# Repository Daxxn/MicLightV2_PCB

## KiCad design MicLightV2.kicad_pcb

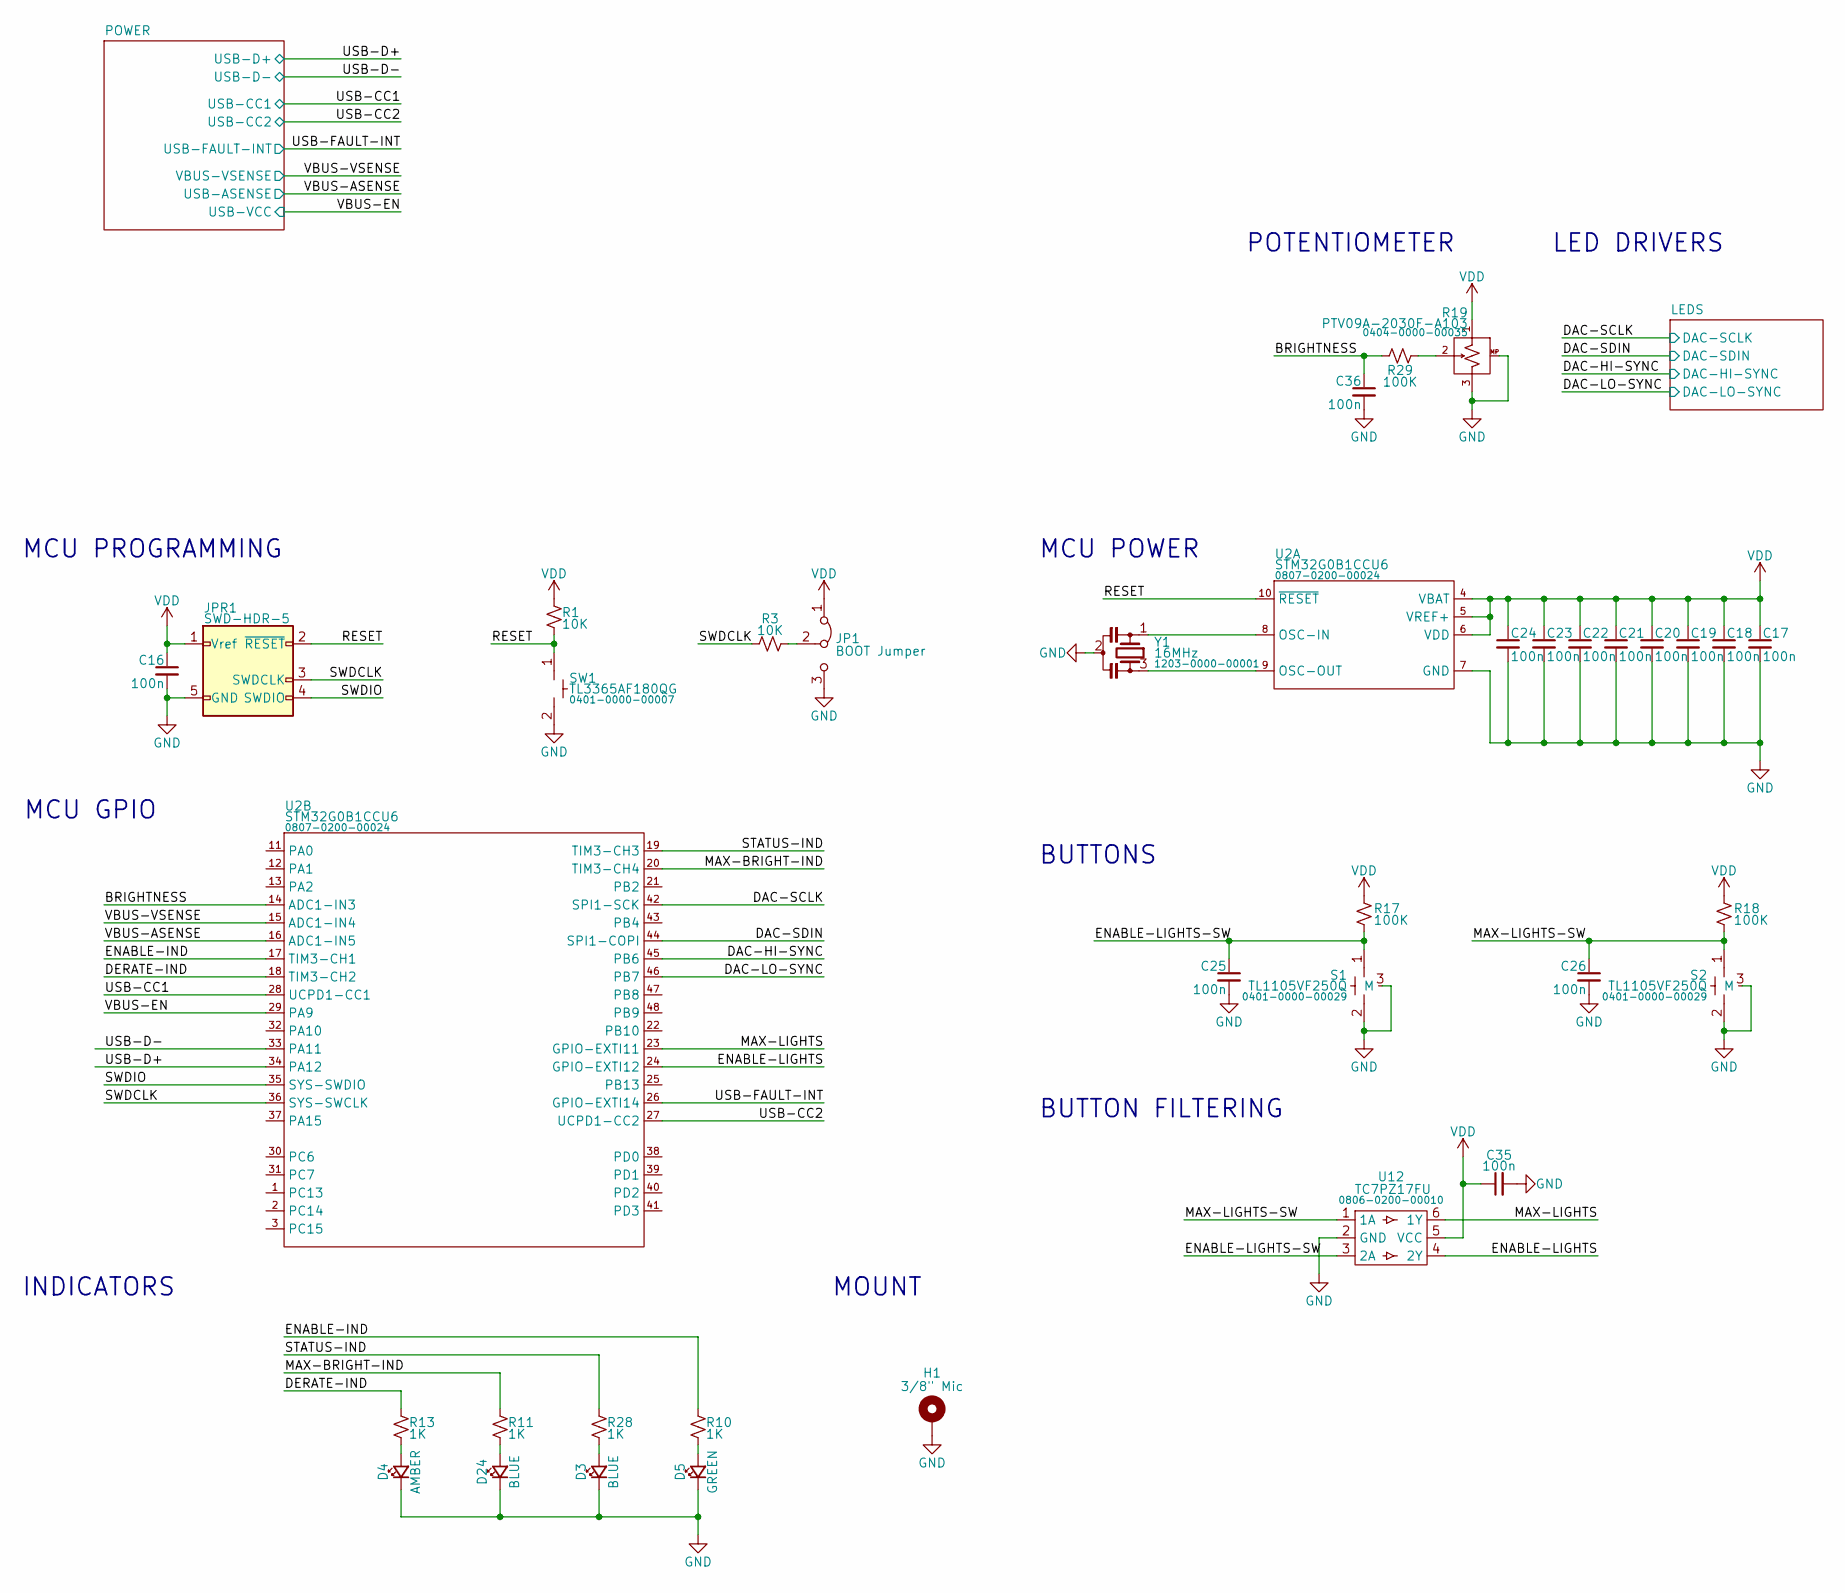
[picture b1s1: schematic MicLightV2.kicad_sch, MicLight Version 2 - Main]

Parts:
C16, C17, C18, C19, C20, C21, C22, C23, C24, C25, C26, C35, C36: 100n; CAP_0402; PartNumber 0201-0100-00001
D3, D24: LTST-S321TBKT; PartNumber 0902-0000-00004
D4: IN-S63AS5UW; LTST-S321TBKT; PartNumber 0902-0000-00002
D5: SM1204SGC; LTST-S321TBKT; PartNumber 0902-0000-00005
H1: 3/8" Mic; MountingHole_0.375in_Mic_Stand
JP1: BOOT Jumper; SolderJumper-3_P1.3mm_Open_RoundedPad1.0x1.5mm
JPR1: SWD-HDR-5; PinHeader_1x05_P2.54mm_Vertical
R1, R3: 10K; RES_0402; PartNumber 0204-0000-00016
R10, R11, R13, R28: 1K; RES_0402; PartNumber 0204-0000-00032
R17, R18, R29: 100K; RES_0402; PartNumber 0204-0000-00013
R19: PTV09A-2030F-A103; PartNumber 0404-0000-00035
S1, S2: TL1105VF250Q; TL1105VF; PartNumber 0401-0000-00029
SW1: TL3365AF180QG; PartNumber 0401-0000-00007
U2: STM32G0B1CCU6; QFN-48-1EP_7x7mm_P0.5mm_EP5.6x5.6mm; PartNumber 0807-0200-00024
U12: TC7PZ17FU; SOT-363_SC-70-6; PartNumber 0806-0200-00010
Y1: 16MHz; Resonator_SMD_3Pin_3.0x1.1mm; PartNumber 1203-0000-00001

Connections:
/BRIGHTNESS: C36.1, R29.1, U2.14 (PA3)
/DAC-HI-SYNC: U2.45 (PB6); also elsewhere on the board
/DAC-LO-SYNC: U2.46 (PB7); also elsewhere on the board
/DAC-SCLK: U2.42 (SPI1-SCK); also elsewhere on the board
/DAC-SDIN: U2.44 (SPI1-COPI); also elsewhere on the board
/DERATE-IND: R13.1, U2.18 (TIM3-CH2)
/ENABLE-IND: R10.1, U2.17 (TIM3-CH1)
/ENABLE-LIGHTS: U2.24 (GPIO-EXTI12), U12.4 (2Y)
/ENABLE-LIGHTS-SW: C25.1, R17.2, S1.1, U12.3 (2A)
/MAX-BRIGHT-IND: R11.1, U2.20 (TIM3-CH4)
/MAX-LIGHTS: U2.23 (GPIO-EXTI11), U12.6 (1Y)
/MAX-LIGHTS-SW: C26.1, R18.2, S2.1, U12.1 (1A)
/RESET: JPR1.2 (~RESET), R1.2, SW1.1, U2.10 (~RESET)
/STATUS-IND: R28.1, U2.19 (TIM3-CH3)
/SWDCLK: JPR1.3 (SWDCLK), R3.1, U2.36 (SYS-SWCLK)
/SWDIO: JPR1.4 (SWDIO), U2.35 (SYS-SWDIO)
/USB-CC1: U2.28 (UCPD1-CC1); also elsewhere on the board
/USB-CC2: U2.27 (UCPD1-CC2); also elsewhere on the board
/USB-D+: U2.34 (PA12); also elsewhere on the board
/USB-D-: U2.33 (PA11); also elsewhere on the board
/USB-FAULT-INT: U2.26 (GPIO-EXTI14); also elsewhere on the board
/VBUS-ASENSE: U2.16 (PA5); also elsewhere on the board
/VBUS-VSENSE: U2.15 (PA4); also elsewhere on the board
GND: C16.2, C17.2, C18.2, C19.2, C20.2, C21.2, C22.2, C23.2, C24.2, C25.2, C26.2, C35.2, C36.2, D3.1 (K), D4.1 (K), D5.1 (K), D24.1 (K), H1.1, JP1.3 (B), JPR1.5 (GND), R19.3 (B), R19.MP (Mount), S1.2, S1.3 (M), S2.2, S2.3 (M), SW1.2, U2.7 (GND), U2.49 (GND), U12.2 (GND), Y1.2; also elsewhere on the board
unnamed: D3.2 (A), R28.2
unnamed: D4.2 (A), R13.2
unnamed: D5.2 (A), R10.2
unnamed: D24.2 (A), R11.2
unnamed: JP1.2 (C), R3.2
unnamed: R19.2 (W), R29.2
unnamed: U2.8 (OSC-IN), Y1.1
unnamed: U2.9 (OSC-OUT), Y1.3
VDD: C16.1, C17.1, C18.1, C19.1, C20.1, C21.1, C22.1, C23.1, C24.1, C35.1, JP1.1 (A), JPR1.1 (Vref), R1.1, R17.1, R18.1, R19.1 (A), U2.4 (VBAT), U2.5 (VREF+), U2.6 (VDD), U12.5 (VCC); also elsewhere on the board

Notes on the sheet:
MCU GPIO
BUTTON FILTERING
INDICATORS
LED DRIVERS
POTENTIOMETER
MCU POWER
MCU PROGRAMMING
MOUNT
BUTTONS

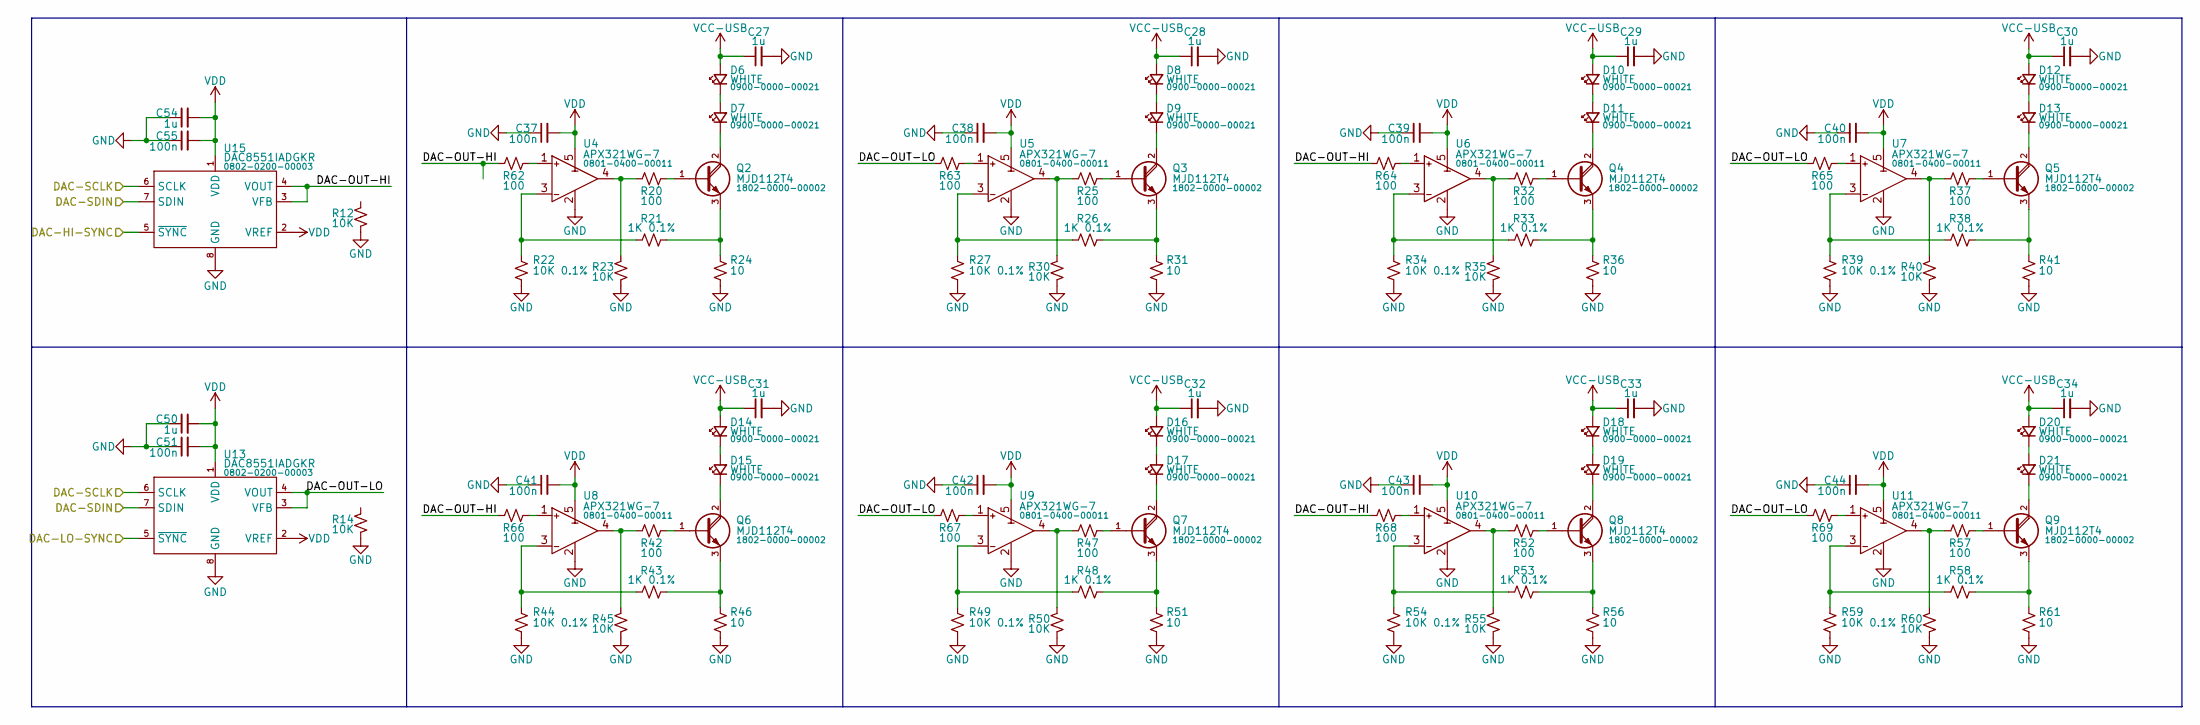
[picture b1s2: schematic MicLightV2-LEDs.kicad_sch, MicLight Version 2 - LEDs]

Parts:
C27, C28, C29, C30, C31, C32, C33, C34: 1u; CAP_0603; PartNumber 0201-0100-00051
C37, C38, C39, C40, C41, C42, C43, C44, C51, C55: 100n; CAP_0402; PartNumber 0201-0100-00001
C50, C54: 1u; CAP_0402; PartNumber 0201-0100-00050
D6, D7, D8, D9, D10, D11, D12, D13, D14, D15, D16, D17, D18, D19, D20, D21: JK3030AWT-P-H40EA0000-N0000001; JK3030AWT; PartNumber 0900-0000-00021
Q2, Q3, Q4, Q5, Q6, Q7, Q8, Q9: MJD112T4; TO-252-2; PartNumber 1802-0000-00002
R12, R14, R23, R30, R35, R40, R45, R50, R55, R60: 10K; RES_0402; PartNumber 0204-0000-00016
R20, R25, R32, R37, R42, R47, R52, R57: 100; RES_0402
R21, R26, R33, R38, R43, R48, R53, R58: 1K 0.1%; RES_0402; PartNumber 0204-0100-00012
R22, R27, R34, R39, R44, R49, R54, R59: 10K 0.1%; RES_0402; PartNumber 0204-0100-00019
R24, R31, R36, R41, R46, R51, R56, R61: 10; RES_1218; PartNumber 0204-0200-00031
R62, R63, R64, R65, R66, R67, R68, R69: 100; RES_0402; PartNumber 0204-0000-00011
U4, U5, U6, U7, U8, U9, U10, U11: APX321WG-7; SOT-23-5; PartNumber 0801-0400-00011
U13, U15: DAC8551IADGKR; VSSOP-8_3.0x3.0mm_P0.65mm; PartNumber 0802-0200-00003

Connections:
/DAC-HI-SYNC: U15.5 (~SYNC); also elsewhere on the board
/DAC-LO-SYNC: U13.5 (~SYNC); also elsewhere on the board
/DAC-SCLK: U13.6 (SCLK), U15.6 (SCLK); also elsewhere on the board
/DAC-SDIN: U13.7 (SDIN), U15.7 (SDIN); also elsewhere on the board
/LEDS/DAC-OUT-HI: R62.1, R64.1, R66.1, R68.1, U15.3 (VFB), U15.4 (VOUT)
/LEDS/DAC-OUT-LO: R63.1, R65.1, R67.1, R69.1, U13.3 (VFB), U13.4 (VOUT)
GND: C27.2, C28.2, C29.2, C30.2, C31.2, C32.2, C33.2, C34.2, C37.1, C38.1, C39.1, C40.1, C41.1, C42.1, C43.1, C44.1, C50.1, C51.1, C54.1, C55.1, R12.2, R14.2, R22.2, R23.2, R24.2, R27.2, R30.2, R31.2, R34.2, R35.2, R36.2, R39.2, R40.2, R41.2, R44.2, R45.2, R46.2, R49.2, R50.2, R51.2, R54.2, R55.2, R56.2, R59.2, R60.2, R61.2, U4.2 (V-), U5.2 (V-), U6.2 (V-), U7.2 (V-), U8.2 (V-), U9.2 (V-), U10.2 (V-), U11.2 (V-), U13.8 (GND), U15.8 (GND); also elsewhere on the board
unnamed: D6.1 (K), D7.2 (A)
unnamed: D7.1 (K), Q2.2 (C)
unnamed: D8.1 (K), D9.2 (A)
unnamed: D9.1 (K), Q3.2 (C)
unnamed: D10.1 (K), D11.2 (A)
unnamed: D11.1 (K), Q4.2 (C)
unnamed: D12.1 (K), D13.2 (A)
unnamed: D13.1 (K), Q5.2 (C)
unnamed: D14.1 (K), D15.2 (A)
unnamed: D15.1 (K), Q6.2 (C)
unnamed: D16.1 (K), D17.2 (A)
unnamed: D17.1 (K), Q7.2 (C)
unnamed: D18.1 (K), D19.2 (A)
unnamed: D19.1 (K), Q8.2 (C)
unnamed: D20.1 (K), D21.2 (A)
unnamed: D21.1 (K), Q9.2 (C)
unnamed: Q2.1 (B), R20.2
unnamed: Q2.3 (E), R21.2, R24.1
unnamed: Q3.1 (B), R25.2
unnamed: Q3.3 (E), R26.2, R31.1
unnamed: Q4.1 (B), R32.2
unnamed: Q4.3 (E), R33.2, R36.1
unnamed: Q5.1 (B), R37.2
unnamed: Q5.3 (E), R38.2, R41.1
unnamed: Q6.1 (B), R42.2
unnamed: Q6.3 (E), R43.2, R46.1
unnamed: Q7.1 (B), R47.2
unnamed: Q7.3 (E), R48.2, R51.1
unnamed: Q8.1 (B), R52.2
unnamed: Q8.3 (E), R53.2, R56.1
unnamed: Q9.1 (B), R57.2
unnamed: Q9.3 (E), R58.2, R61.1
unnamed: R62.2, U4.1 (IN+)
unnamed: R21.1, R22.1, U4.3 (IN-)
unnamed: R20.1, R23.1, U4.4 (OUT)
unnamed: R63.2, U5.1 (IN+)
unnamed: R26.1, R27.1, U5.3 (IN-)
unnamed: R25.1, R30.1, U5.4 (OUT)
unnamed: R64.2, U6.1 (IN+)
unnamed: R33.1, R34.1, U6.3 (IN-)
unnamed: R32.1, R35.1, U6.4 (OUT)
unnamed: R65.2, U7.1 (IN+)
unnamed: R38.1, R39.1, U7.3 (IN-)
unnamed: R37.1, R40.1, U7.4 (OUT)
unnamed: R66.2, U8.1 (IN+)
unnamed: R43.1, R44.1, U8.3 (IN-)
unnamed: R42.1, R45.1, U8.4 (OUT)
unnamed: R67.2, U9.1 (IN+)
unnamed: R48.1, R49.1, U9.3 (IN-)
unnamed: R47.1, R50.1, U9.4 (OUT)
unnamed: R68.2, U10.1 (IN+)
unnamed: R53.1, R54.1, U10.3 (IN-)
unnamed: R52.1, R55.1, U10.4 (OUT)
unnamed: R69.2, U11.1 (IN+)
unnamed: R58.1, R59.1, U11.3 (IN-)
unnamed: R57.1, R60.1, U11.4 (OUT)
VCC-USB: C27.1, C28.1, C29.1, C30.1, C31.1, C32.1, C33.1, C34.1, D6.2 (A), D8.2 (A), D10.2 (A), D12.2 (A), D14.2 (A), D16.2 (A), D18.2 (A), D20.2 (A); also elsewhere on the board
VDD: C37.2, C38.2, C39.2, C40.2, C41.2, C42.2, C43.2, C44.2, C50.2, C51.2, C54.2, C55.2, U4.5 (V+), U5.5 (V+), U6.5 (V+), U7.5 (V+), U8.5 (V+), U9.5 (V+), U10.5 (V+), U11.5 (V+), U13.1 (VDD), U13.2 (VREF), U15.1 (VDD), U15.2 (VREF); also elsewhere on the board

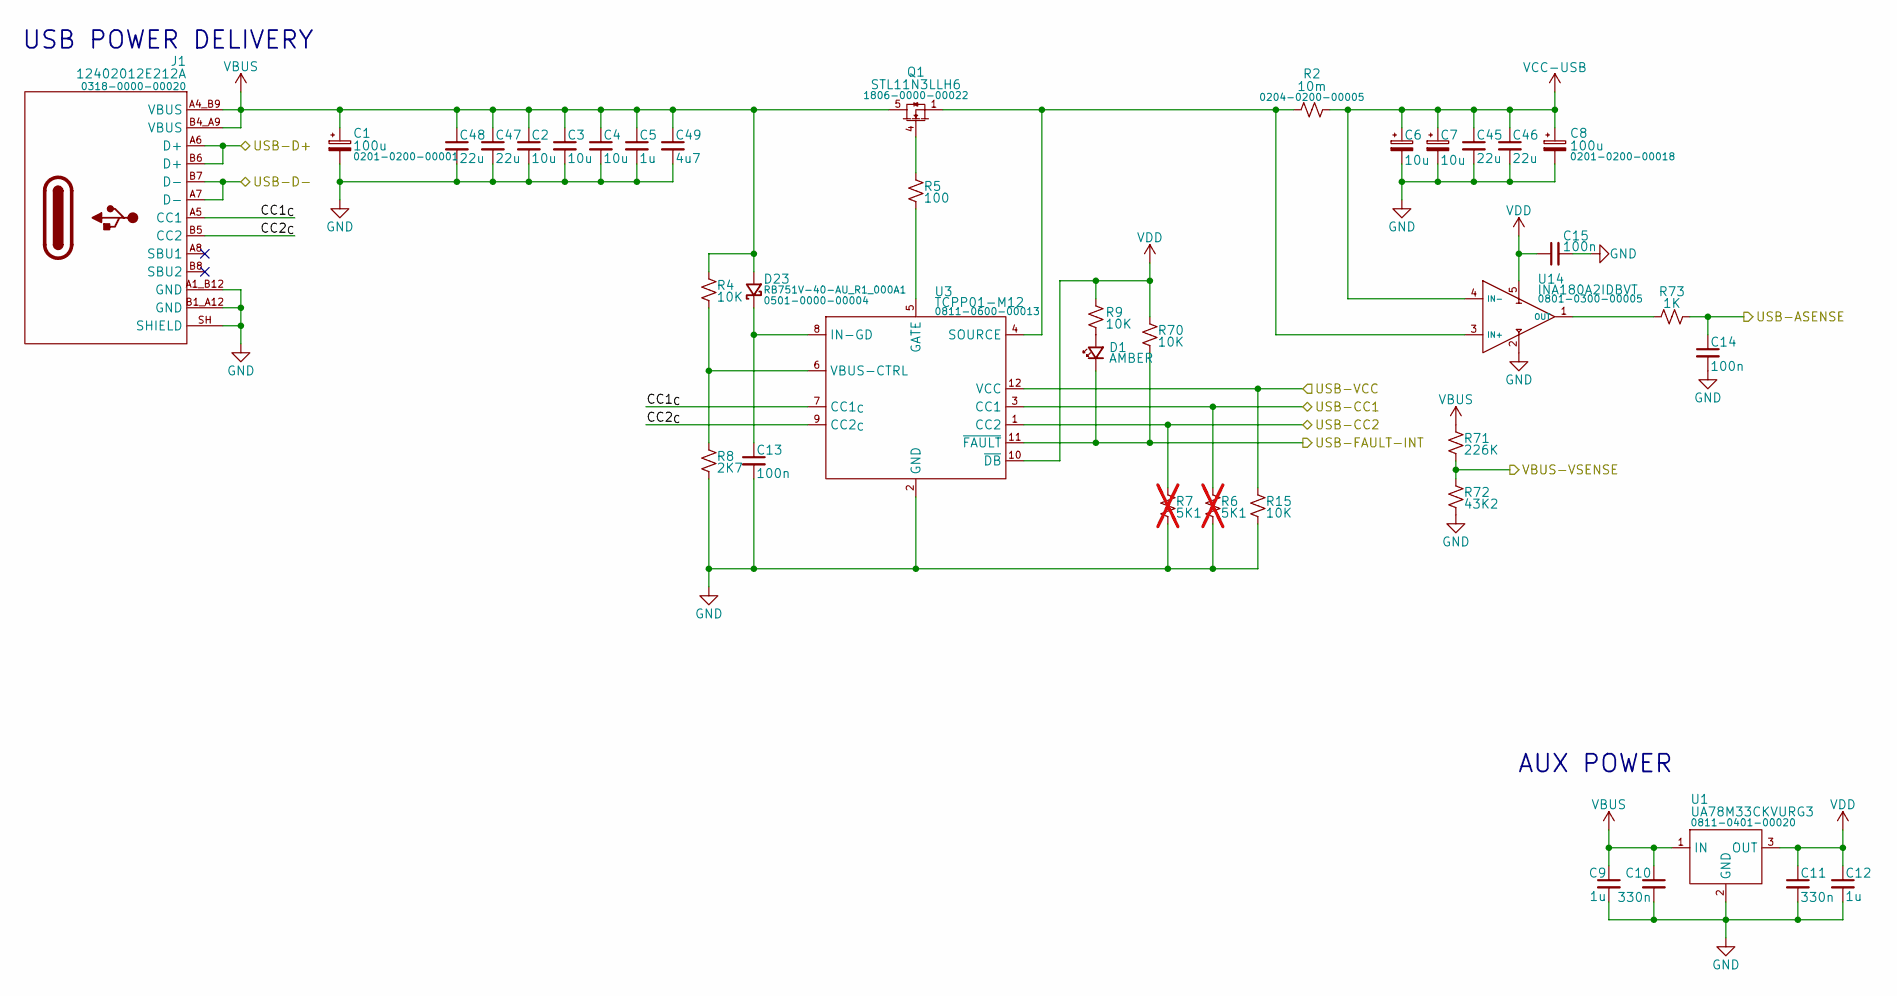
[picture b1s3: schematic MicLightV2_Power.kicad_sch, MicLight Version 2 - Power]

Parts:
C1: 100u; CAP_EL_8x10; PartNumber 0201-0200-00001
C2, C3, C4: 10u; CAP_1210; PartNumber 0201-0100-00040
C5, C9, C12: 1u; CAP_0603; PartNumber 0201-0100-00051
C6, C7: 10u; C-TANT-1210_EIA-3528; PartNumber 0201-0300-00008
C8: 100u; CAP_EL_6.3x7.7; PartNumber 0201-0200-00018
C10, C11: 330n; CAP_0402
C13, C15: 100n; CAP_0402; PartNumber 0201-0100-00001
C14: 100n; CAP_0402
C45, C46, C47, C48: 22u; CAP_1206; PartNumber 0201-0100-00067
C49: 4u7; CAP_0805; PartNumber 0201-0100-00074
D1: IN-S63AS5UW; LTST-S321TBKT; PartNumber 0902-0000-00002
D23: RB751V-40-AU_R1_000A1; D_SOD-323; PartNumber 0501-0000-00004
J1: 12402012E212A; PartNumber 0318-0000-00020
Q1: STL11N3LLH6; POWERFLAT_3.3MM; PartNumber 1806-0000-00022
R2: 10m; RES_1206; PartNumber 0204-0200-00005
R4, R9, R15, R70: 10K; RES_0402; PartNumber 0204-0000-00016
R5: 100; RES_0402; PartNumber 0204-0000-00011
R6, R7: 5K1; RES_0402; PartNumber 0204-0000-00115; not fitted
R8: 2K7; RES_0402; PartNumber 0204-0000-00121
R71: 226K; RES_0402; PartNumber 0204-0000-00048
R72: 43K2; RES_0402; PartNumber 0204-0000-00110
R73: 1K; RES_0402
U1: UA78M33CKVURG3; TO-252-2; PartNumber 0811-0401-00020
U3: TCPP01-M12; QFN-12-1EP_3x3mm_P0.5mm_EP1.45x1.45mm; PartNumber 0811-0600-00013
U14: INA180A2IDBVT; SOT-23-5; PartNumber 0801-0300-00005

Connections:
/POWER/CC1_{C}: J1.A5 (CC1), U3.7 (CC1_{C})
/POWER/CC2_{C}: J1.B5 (CC2), U3.9 (CC2_{C})
/USB-CC1: R6.1, U3.3 (CC1); also elsewhere on the board
/USB-CC2: R7.1, U3.1 (CC2); also elsewhere on the board
/USB-D+: J1.A6 (D+), J1.B6 (D+); also elsewhere on the board
/USB-D-: J1.A7 (D-), J1.B7 (D-); also elsewhere on the board
/USB-FAULT-INT: D1.1 (K), R70.2, U3.11 (~FAULT); also elsewhere on the board
/VBUS-ASENSE: C14.1, R73.2; also elsewhere on the board
/VBUS-VSENSE: R71.2, R72.1; also elsewhere on the board
GND: C1.2 (-), C2.2, C3.2, C4.2, C5.2, C6.2, C7.2, C8.2 (-), C9.2, C10.2, C11.2, C12.2, C13.2, C14.2, C15.2, C45.2, C46.2, C47.2, C48.2, C49.2, J1.A1_B12 (GND), J1.B1_A12 (GND), J1.SH (SHIELD), R6.2, R7.2, R8.2, R15.2, R72.2, U1.2 (GND), U3.2 (GND), U3.13 (GND), U14.2 (GND); also elsewhere on the board
unnamed: D1.2 (A), R9.2
unnamed: C13.1, D23.1 (K), U3.8 (IN-GD)
unnamed: Q1.4 (G), R5.1
unnamed: R5.2, U3.5 (GATE)
unnamed: R4.2, R8.1, U3.6 (VBUS-CTRL)
unnamed: R73.1, U14.1 (OUT)
S: Q1.1 (S), Q1.2 (S), Q1.3 (S), R2.1, U3.4 (SOURCE), U14.3 (IN+)
VBUS: C1.1 (+), C2.1, C3.1, C4.1, C5.1, C9.1, C10.1, C47.1, C48.1, C49.1, D23.2 (A), J1.A4_B9 (VBUS), J1.B4_A9 (VBUS), Q1.5 (D), R4.1, R71.1, U1.1 (IN)
VCC-USB: C6.1, C7.1, C8.1 (+), C45.1, C46.1, R2.2, U14.4 (IN-); also elsewhere on the board
VDD: C11.1, C12.1, C15.1, R9.1, R15.1, R70.1, U1.3 (OUT), U3.10 (~DB), U3.12 (VCC), U14.5 (VS); also elsewhere on the board

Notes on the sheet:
USB POWER DELIVERY
AUX POWER

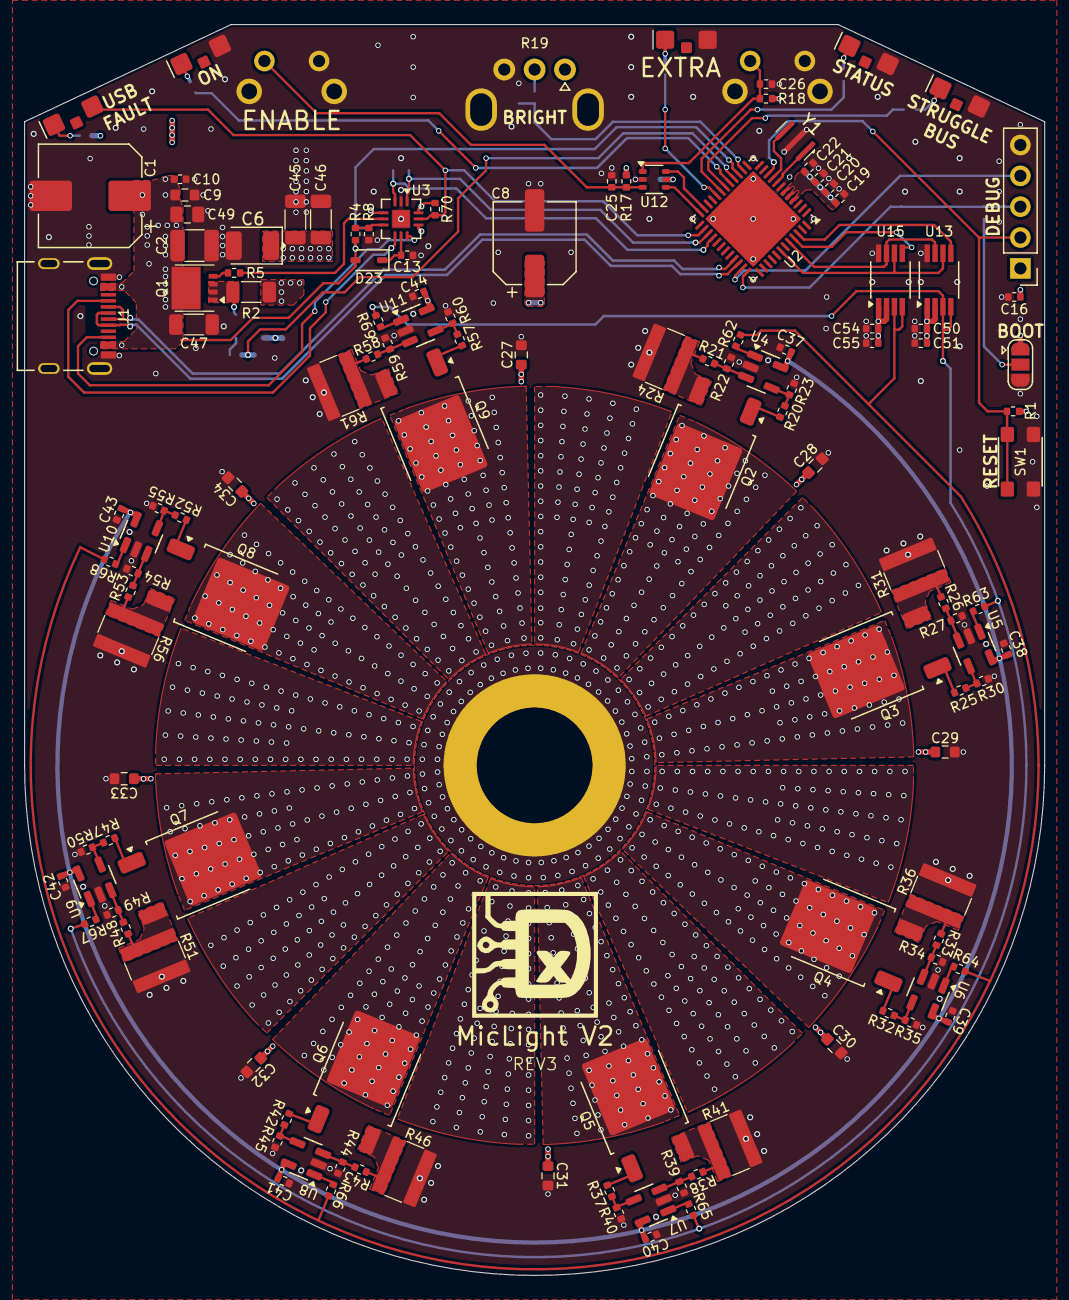
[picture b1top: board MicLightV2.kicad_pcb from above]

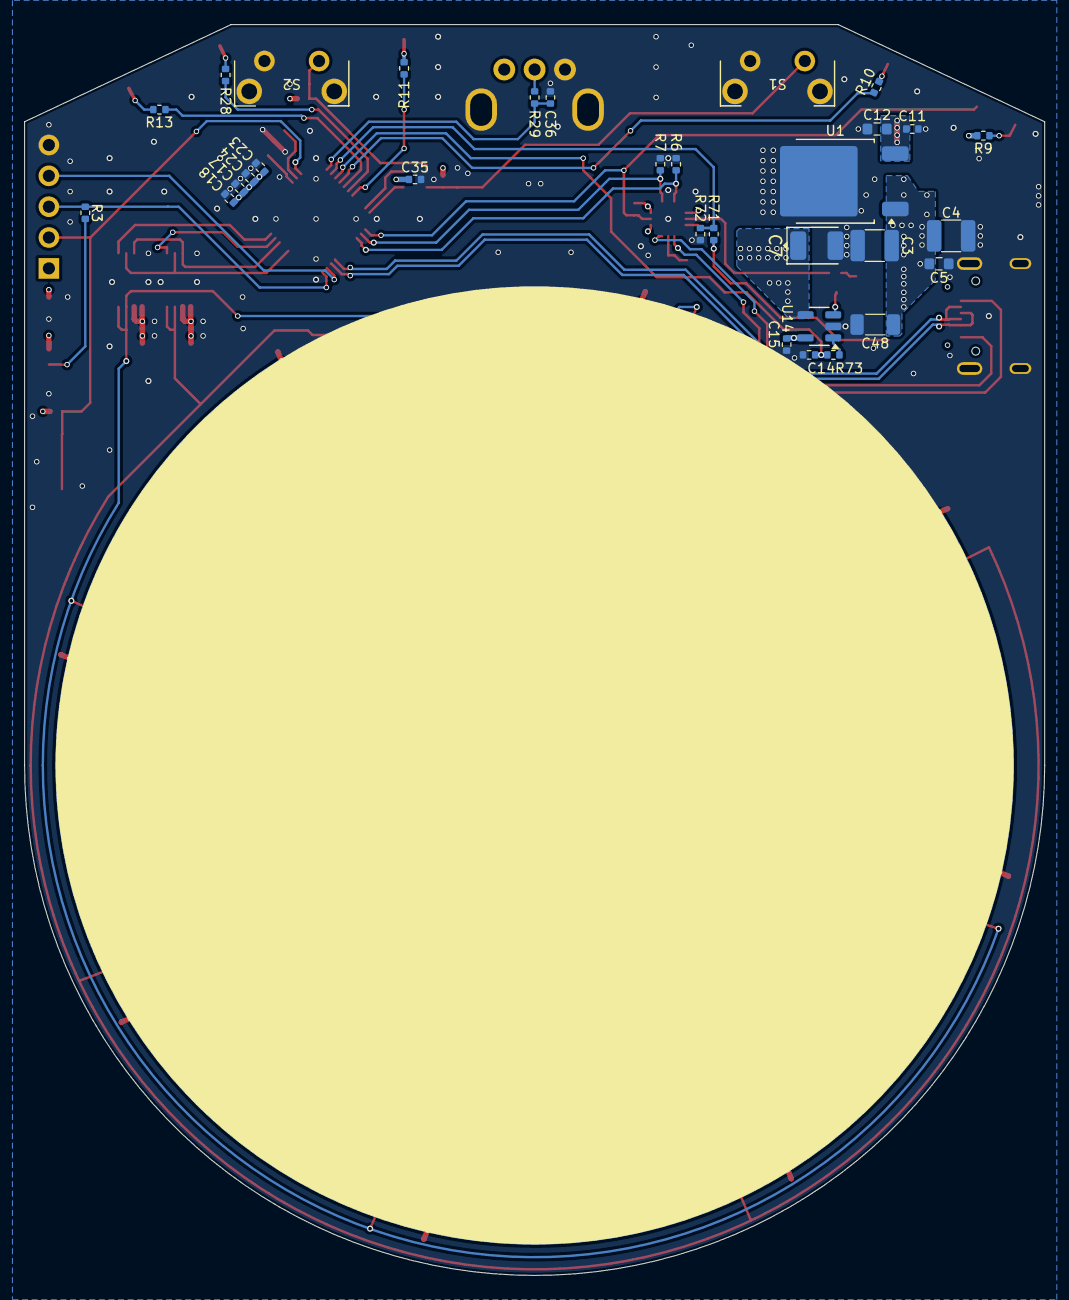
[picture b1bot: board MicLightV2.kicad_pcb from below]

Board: 4 copper layers, 84.0 x 103.0 mm, 176 parts (47 on the bottom side), 102 nets.

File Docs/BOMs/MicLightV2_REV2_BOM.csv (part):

"Reference","Value","PartNumber","Datasheet","Description","Color"
"C1","100u","0201-0200-00001","${DATASHEETS}/UWT.pdf","CAP ALUM 100uF 50V 140mA@120Hz ±20% SMD,D8xL10mm Aluminum Electrolytic Capacitors - SMD ROHS",""
"C2","10u","0201-0100-00040","${DATASHEETS}/CL32A106KAULNNE.pdf","CAP CER 10UF 25V X5R 1210",""
"C3","10u","0201-0100-00040","${DATASHEETS}/CL32A106KAULNNE.pdf","CAP CER 10UF 25V X5R 1210",""
"C4","10u","0201-0100-00040","${DATASHEETS}/CL32A106KAULNNE.pdf","CAP CER 10UF 25V X5R 1210",""
"C5","1u","0201-0100-00051","${DATASHEETS}/CL10A105KA8NNNC.pdf","CAP CER 1UF 25V X5R 0603",""
"C6","10u","0201-0300-00008","${DATASHEETS}/TCJ.pdf","10 µF Molded Tantalum Polymer Capacitor 35 V 1210 (3528 Metric) 200mOhm @ 100kHz",""
"C7","10u","0201-0300-00008","${DATASHEETS}/TCJ.pdf","10 µF Molded Tantalum Polymer Capacitor 35 V 1210 (3528 Metric) 200mOhm @ 100kHz",""
"C8","100u","0201-0200-00018","~","CAP ALUM 100uF 25V 6.3x7.7 Hilitchi Kit",""
"C9","1u","0201-0100-00051","${DATASHEETS}/CL10A105KA8NNNC.pdf","CAP CER 1UF 25V X5R 0603",""
"C10","330n","","~","Unpolarized Capacitor",""
"C11","330n","","~","Unpolarized Capacitor",""
"C12","1u","0201-0100-00051","${DATASHEETS}/CL10A105KA8NNNC.pdf","CAP CER 1UF 25V X5R 0603",""
"C13","100n","0201-0100-00086","${DATASHEETS}/CL05A104KA5NNNC.pdf","CAP CER 100nF 0.1UF 25V X5R 0402",""
"C14","1u","0201-0100-00050","${DATASHEETS}/CL05A105KO5NNNC.pdf","CAP CER 1UF 16V X5R 0402",""
"C15","100n","0201-0100-00086","${DATASHEETS}/CL05A104KA5NNNC.pdf","CAP CER 100nF 0.1UF 25V X5R 0402",""
"C16","100n","0201-0100-00086","${DATASHEETS}/CL05A104KA5NNNC.pdf","CAP CER 100nF 0.1UF 25V X5R 0402",""
"C17","100n","0201-0100-00086","${DATASHEETS}/CL05A104KA5NNNC.pdf","CAP CER 100nF 0.1UF 25V X5R 0402",""
"C18","100n","0201-0100-00086","${DATASHEETS}/CL05A104KA5NNNC.pdf","CAP CER 100nF 0.1UF 25V X5R 0402",""
"C19","100n","0201-0100-00086","${DATASHEETS}/CL05A104KA5NNNC.pdf","CAP CER 100nF 0.1UF 25V X5R 0402",""
"C20","100n","0201-0100-00086","${DATASHEETS}/CL05A104KA5NNNC.pdf","CAP CER 100nF 0.1UF 25V X5R 0402",""
"C21","100n","0201-0100-00086","${DATASHEETS}/CL05A104KA5NNNC.pdf","CAP CER 100nF 0.1UF 25V X5R 0402",""
"C22","100n","0201-0100-00086","${DATASHEETS}/CL05A104KA5NNNC.pdf","CAP CER 100nF 0.1UF 25V X5R 0402",""
"C23","100n","0201-0100-00086","${DATASHEETS}/CL05A104KA5NNNC.pdf","CAP CER 100nF 0.1UF 25V X5R 0402",""
"C24","100n","0201-0100-00086","${DATASHEETS}/CL05A104KA5NNNC.pdf","CAP CER 100nF 0.1UF 25V X5R 0402",""
"C25","100n","0201-0100-00086","${DATASHEETS}/CL05A104KA5NNNC.pdf","CAP CER 100nF 0.1UF 25V X5R 0402",""
"C26","100n","0201-0100-00086","${DATASHEETS}/CL05A104KA5NNNC.pdf","CAP CER 100nF 0.1UF 25V X5R 0402",""
"C27","1u","0201-0100-00051","${DATASHEETS}/CL10A105KA8NNNC.pdf","CAP CER 1UF 25V X5R 0603",""
"C28","1u","0201-0100-00051","${DATASHEETS}/CL10A105KA8NNNC.pdf","CAP CER 1UF 25V X5R 0603",""
"C29","1u","0201-0100-00051","${DATASHEETS}/CL10A105KA8NNNC.pdf","CAP CER 1UF 25V X5R 0603",""
"C30","1u","0201-0100-00051","${DATASHEETS}/CL10A105KA8NNNC.pdf","CAP CER 1UF 25V X5R 0603",""
"C31","1u","0201-0100-00051","${DATASHEETS}/CL10A105KA8NNNC.pdf","CAP CER 1UF 25V X5R 0603",""
"C32","1u","0201-0100-00051","${DATASHEETS}/CL10A105KA8NNNC.pdf","CAP CER 1UF 25V X5R 0603",""
"C33","1u","0201-0100-00051","${DATASHEETS}/CL10A105KA8NNNC.pdf","CAP CER 1UF 25V X5R 0603",""
"C34","1u","0201-0100-00051","${DATASHEETS}/CL10A105KA8NNNC.pdf","CAP CER 1UF 25V X5R 0603",""
"C35","100n","0201-0100-00086","${DATASHEETS}/CL05A104KA5NNNC.pdf","CAP CER 100nF 0.1UF 25V X5R 0402",""
"C36","100n","0201-0100-00086","${DATASHEETS}/CL05A104KA5NNNC.pdf","CAP CER 100nF 0.1UF 25V X5R 0402",""
"C37","100n","0201-0100-00086","${DATASHEETS}/CL05A104KA5NNNC.pdf","CAP CER 100nF 0.1UF 25V X5R 0402",""
"C38","100n","0201-0100-00086","${DATASHEETS}/CL05A104KA5NNNC.pdf","CAP CER 100nF 0.1UF 25V X5R 0402",""
"C39","100n","0201-0100-00086","${DATASHEETS}/CL05A104KA5NNNC.pdf","CAP CER 100nF 0.1UF 25V X5R 0402",""
"C40","100n","0201-0100-00086","${DATASHEETS}/CL05A104KA5NNNC.pdf","CAP CER 100nF 0.1UF 25V X5R 0402",""
"C41","100n","0201-0100-00086","${DATASHEETS}/CL05A104KA5NNNC.pdf","CAP CER 100nF 0.1UF 25V X5R 0402",""
"C42","100n","0201-0100-00086","${DATASHEETS}/CL05A104KA5NNNC.pdf","CAP CER 100nF 0.1UF 25V X5R 0402",""
"C43","100n","0201-0100-00086","${DATASHEETS}/CL05A104KA5NNNC.pdf","CAP CER 100nF 0.1UF 25V X5R 0402",""
"C44","100n","0201-0100-00086","${DATASHEETS}/CL05A104KA5NNNC.pdf","CAP CER 100nF 0.1UF 25V X5R 0402",""
"C45","22u","0201-0100-00067","${DATASHEETS}/C3216X5R1V226M160AC.pdf","CAP CER 22UF 35V X5R 1206",""
"C46","22u","0201-0100-00067","${DATASHEETS}/C3216X5R1V226M160AC.pdf","CAP CER 22UF 35V X5R 1206",""
"C47","22u","0201-0100-00067","${DATASHEETS}/C3216X5R1V226M160AC.pdf","CAP CER 22UF 35V X5R 1206",""
"C48","22u","0201-0100-00067","${DATASHEETS}/C3216X5R1V226M160AC.pdf","CAP CER 22UF 35V X5R 1206",""
"C49","4u7","0201-0100-00074","${DATASHEETS}/CL21A475KLCLQNC.pdf","CAP CER 4.7UF 35V X5R 0805",""
"C50","1u","0201-0100-00050","${DATASHEETS}/CL05A105KO5NNNC.pdf","CAP CER 1UF 16V X5R 0402",""
"C51","100n","0201-0100-00086","${DATASHEETS}/CL05A104KA5NNNC.pdf","CAP CER 100nF 0.1UF 25V X5R 0402",""
"C54","1u","0201-0100-00050","${DATASHEETS}/CL05A105KO5NNNC.pdf","CAP CER 1UF 16V X5R 0402",""
"C55","100n","0201-0100-00086","${DATASHEETS}/CL05A104KA5NNNC.pdf","CAP CER 100nF 0.1UF 25V X5R 0402",""
"D1","CZ2-0603-GREEN","0900-0000-00038","~","LED SMD Green 0603 Chanzon","GREEN"
"D2","CZ2-0603-GREEN","0900-0000-00038","~","LED SMD Green 0603 Chanzon","GREEN"
"D3","CZ1-0603-BLUE","0900-0000-00037","~","LED SMD Blue 0603 Chanzon","BLUE"
"D4","CZ3-0603-ORANGE","0900-0000-00039","~","LED SMD Orange 0603 Chanzon","ORANGE"
"D5","CZ3-0603-ORANGE","0900-0000-00039","~","LED SMD Orange 0603 Chanzon","ORANGE"
"D6","JK3030AWT-P-H40EA0000-N0000001","0900-0000-00021","${DATASHEETS}/JSeries-3030.pdf","LED J NEUTRAL WHT 4000K SMD","WHITE"
"D7","JK3030AWT-P-H40EA0000-N0000001","0900-0000-00021","${DATASHEETS}/JSeries-3030.pdf","LED J NEUTRAL WHT 4000K SMD","WHITE"
"D8","JK3030AWT-P-H40EA0000-N0000001","0900-0000-00021","${DATASHEETS}/JSeries-3030.pdf","LED J NEUTRAL WHT 4000K SMD","WHITE"
"D9","JK3030AWT-P-H40EA0000-N0000001","0900-0000-00021","${DATASHEETS}/JSeries-3030.pdf","LED J NEUTRAL WHT 4000K SMD","WHITE"
"D10","JK3030AWT-P-H40EA0000-N0000001","0900-0000-00021","${DATASHEETS}/JSeries-3030.pdf","LED J NEUTRAL WHT 4000K SMD","WHITE"
"D11","JK3030AWT-P-H40EA0000-N0000001","0900-0000-00021","${DATASHEETS}/JSeries-3030.pdf","LED J NEUTRAL WHT 4000K SMD","WHITE"
"D12","JK3030AWT-P-H40EA0000-N0000001","0900-0000-00021","${DATASHEETS}/JSeries-3030.pdf","LED J NEUTRAL WHT 4000K SMD","WHITE"
"D13","JK3030AWT-P-H40EA0000-N0000001","0900-0000-00021","${DATASHEETS}/JSeries-3030.pdf","LED J NEUTRAL WHT 4000K SMD","WHITE"
"D14","JK3030AWT-P-H40EA0000-N0000001","0900-0000-00021","${DATASHEETS}/JSeries-3030.pdf","LED J NEUTRAL WHT 4000K SMD","WHITE"
"D15","JK3030AWT-P-H40EA0000-N0000001","0900-0000-00021","${DATASHEETS}/JSeries-3030.pdf","LED J NEUTRAL WHT 4000K SMD","WHITE"
"D16","JK3030AWT-P-H40EA0000-N0000001","0900-0000-00021","${DATASHEETS}/JSeries-3030.pdf","LED J NEUTRAL WHT 4000K SMD","WHITE"
"D17","JK3030AWT-P-H40EA0000-N0000001","0900-0000-00021","${DATASHEETS}/JSeries-3030.pdf","LED J NEUTRAL WHT 4000K SMD","WHITE"
"D18","JK3030AWT-P-H40EA0000-N0000001","0900-0000-00021","${DATASHEETS}/JSeries-3030.pdf","LED J NEUTRAL WHT 4000K SMD","WHITE"
"D19","JK3030AWT-P-H40EA0000-N0000001","0900-0000-00021","${DATASHEETS}/JSeries-3030.pdf","LED J NEUTRAL WHT 4000K SMD","WHITE"
"D20","JK3030AWT-P-H40EA0000-N0000001","0900-0000-00021","${DATASHEETS}/JSeries-3030.pdf","LED J NEUTRAL WHT 4000K SMD","WHITE"
"D21","JK3030AWT-P-H40EA0000-N0000001","0900-0000-00021","${DATASHEETS}/JSeries-3030.pdf","LED J NEUTRAL WHT 4000K SMD","WHITE"
"D22","CZ1-0603-BLUE","0900-0000-00037","~","LED SMD Blue 0603 Chanzon","BLUE"
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
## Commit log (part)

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2025-03-22 Finish REV1 - Sent to board house.
2025-03-22 Remove KiCad lock file
2025-08-30 REV1
2025-09-01 REV2 - add DAC and cc led drivers
